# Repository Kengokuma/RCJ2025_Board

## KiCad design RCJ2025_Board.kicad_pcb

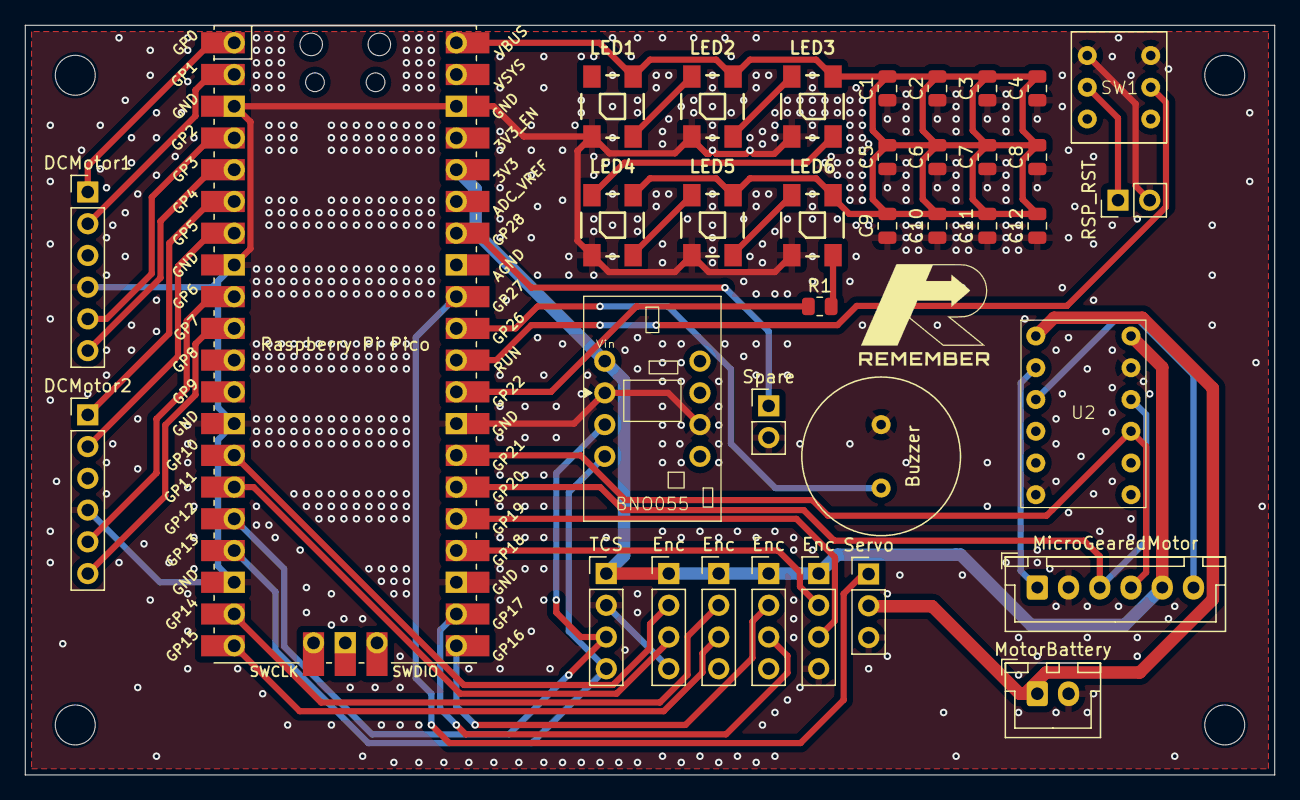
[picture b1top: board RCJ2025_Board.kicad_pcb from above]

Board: 2 copper layers, 100.0 x 60.0 mm, 36 parts (0 on the bottom side), 38 nets.

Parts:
BNO055: BNO055
Buzzer: Buzzer
C1, C2, C3, C4, C5, C6, C7, C8, C9, C10, C11, C12: 0.1; C_0805_2012Metric
DCMotor1: DCMotor1; PinHeader_1x06_P2.54mm_Vertical
DCMotor2: DCMotor2; PinHeader_1x06_P2.54mm_Vertical
Enc: Encoder1; PinHeader_1x04_P2.54mm_Vertical
Enc#2, Enc#3, Enc#4: Encoder1; PinHeader_1x04_P2.54mm_Vertical
LED1, LED2, LED3, LED4, LED5, LED6: WS2812B
MicroGearedMotor: MicroGearedMotor; JST_XH_B6B-XH-A_1x06_P2.50mm_Vertical
MotorBattery: MotorBattery; JST_XH_B2B-XH-A_1x02_P2.50mm_Vertical
R1: 470; R_0805_2012Metric
RSP_RST: RSP_RESET; PinHeader_1x02_P2.54mm_Vertical
Raspberry Pi Pico: Pico; RPi_Pico_SMD_TH
SW1: SW_DPDT_x2; ToggleSwitch_DPDT
Servo: Servo; PinHeader_1x03_P2.54mm_Vertical
Spare: Spare; PinHeader_1x02_P2.54mm_Vertical
TCS: TCS34725; PinHeader_1x04_P2.54mm_Vertical
U2: DRV8835

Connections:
3.3V: BNO055.1 (VIN), Enc.1, Enc#2.1, Enc#3.1, Enc#4.1, MicroGearedMotor.5, Raspberry Pi Pico.36 (3V3), TCS.1, U2.7 (VCC)
5V: C1.2, C2.2, C3.2, C4.2, C5.2, C6.2, C7.2, C8.2, C9.2, C10.2, C11.2, C12.2, LED1.1 (VCC), LED2.1 (VCC), LED3.1 (VCC), LED4.1 (VCC), LED5.1 (VCC), LED6.1 (VCC), Raspberry Pi Pico.40 (VBUS)
6V: MotorBattery.1, Servo.2, U2.1 (VM)
A1: Enc.2, Raspberry Pi Pico.14 (GPIO10)
A2: Enc#4.2, Raspberry Pi Pico.19 (GPIO14)
A3: Enc#3.2, Raspberry Pi Pico.21 (GPIO16)
A4: Enc#2.2, Raspberry Pi Pico.24 (GPIO18)
A5: MicroGearedMotor.3, Raspberry Pi Pico.26 (GPIO20), U2.9 (AIN1)
B1: Enc.3, Raspberry Pi Pico.15 (GPIO11)
B2: Enc#4.3, Raspberry Pi Pico.20 (GPIO15)
B3: Enc#3.3, Raspberry Pi Pico.22 (GPIO17)
B4: Enc#2.3, Raspberry Pi Pico.25 (GPIO19)
B5: MicroGearedMotor.4, Raspberry Pi Pico.27 (GPIO21), U2.10 (AIN2)
Buzzer: Buzzer.1 (-), Raspberry Pi Pico.31 (GPIO26_ADC0)
GND: BNO055.2 (GND), BNO055.6 (GND), Buzzer.2 (+), C1.1, C2.1, C3.1, C4.1, C5.1, C6.1, C7.1, C8.1, C9.1, C10.1, C11.1, C12.1, DCMotor1.4, DCMotor2.4, Enc.4, Enc#2.4, Enc#3.4, Enc#4.4, LED1.3 (GND), LED2.3 (GND), LED3.3 (GND), LED4.3 (GND), LED5.3 (GND), LED6.3 (GND), MicroGearedMotor.2, MotorBattery.2, RSP_RST.2, Raspberry Pi Pico.3 (GND), Raspberry Pi Pico.8 (GND), Raspberry Pi Pico.13 (GND), Raspberry Pi Pico.18 (GND), Raspberry Pi Pico.23 (GND), Raspberry Pi Pico.28 (GND), Raspberry Pi Pico.38 (GND), SW1.1 (A), SW1.4 (A), Servo.3, Spare.2, TCS.2, U2.6 (GND), U2.8 (MODE)
GPIO_RSP: RSP_RST.1, SW1.2 (B)
LED: R1.1, Raspberry Pi Pico.29 (GPIO22)
M1: MicroGearedMotor.1, U2.2 (AOUT1)
M2: MicroGearedMotor.6, U2.3 (AOUT2)
unnamed: LED1.4 (DIN), LED2.2 (DOUT)
unnamed: LED2.4 (DIN), LED3.2 (DOUT)
unnamed: LED3.4 (DIN), LED4.2 (DOUT)
unnamed: LED4.4 (DIN), LED5.2 (DOUT)
unnamed: LED5.4 (DIN), LED6.2 (DOUT)
unnamed: LED6.4 (DIN), R1.2
PWM1_A: DCMotor1.1, Raspberry Pi Pico.1 (GPIO0)
PWM1_B: DCMotor1.2, Raspberry Pi Pico.2 (GPIO1)
PWM2_A: DCMotor1.5, Raspberry Pi Pico.4 (GPIO2)
PWM2_B: DCMotor1.6, Raspberry Pi Pico.5 (GPIO3)
PWM3_A: DCMotor2.1, Raspberry Pi Pico.6 (GPIO4)
PWM3_B: DCMotor2.2, Raspberry Pi Pico.7 (GPIO5)
PWM4_A: DCMotor2.5, Raspberry Pi Pico.9 (GPIO6)
PWM4_B: DCMotor2.6, Raspberry Pi Pico.10 (GPIO7)
RUN: Raspberry Pi Pico.30 (RUN), SW1.5 (B)
SCL: BNO055.4 (SCL), Raspberry Pi Pico.17 (GPIO13), TCS.4
SDA: BNO055.3 (SDA), Raspberry Pi Pico.16 (GPIO12), TCS.3
Servo: Raspberry Pi Pico.32 (GPIO27_ADC1), Servo.1
Spare: Raspberry Pi Pico.34 (GPIO28_ADC2), Spare.1

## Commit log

2025-08-13 基板外形を作成
    マウンティングホールを追加
    ベタを作成
2025-08-15 完成間際の絶望的状況
2025-08-15 ほぼ完成。最終確認待ち
2025-08-15 ロゴマークを追加
